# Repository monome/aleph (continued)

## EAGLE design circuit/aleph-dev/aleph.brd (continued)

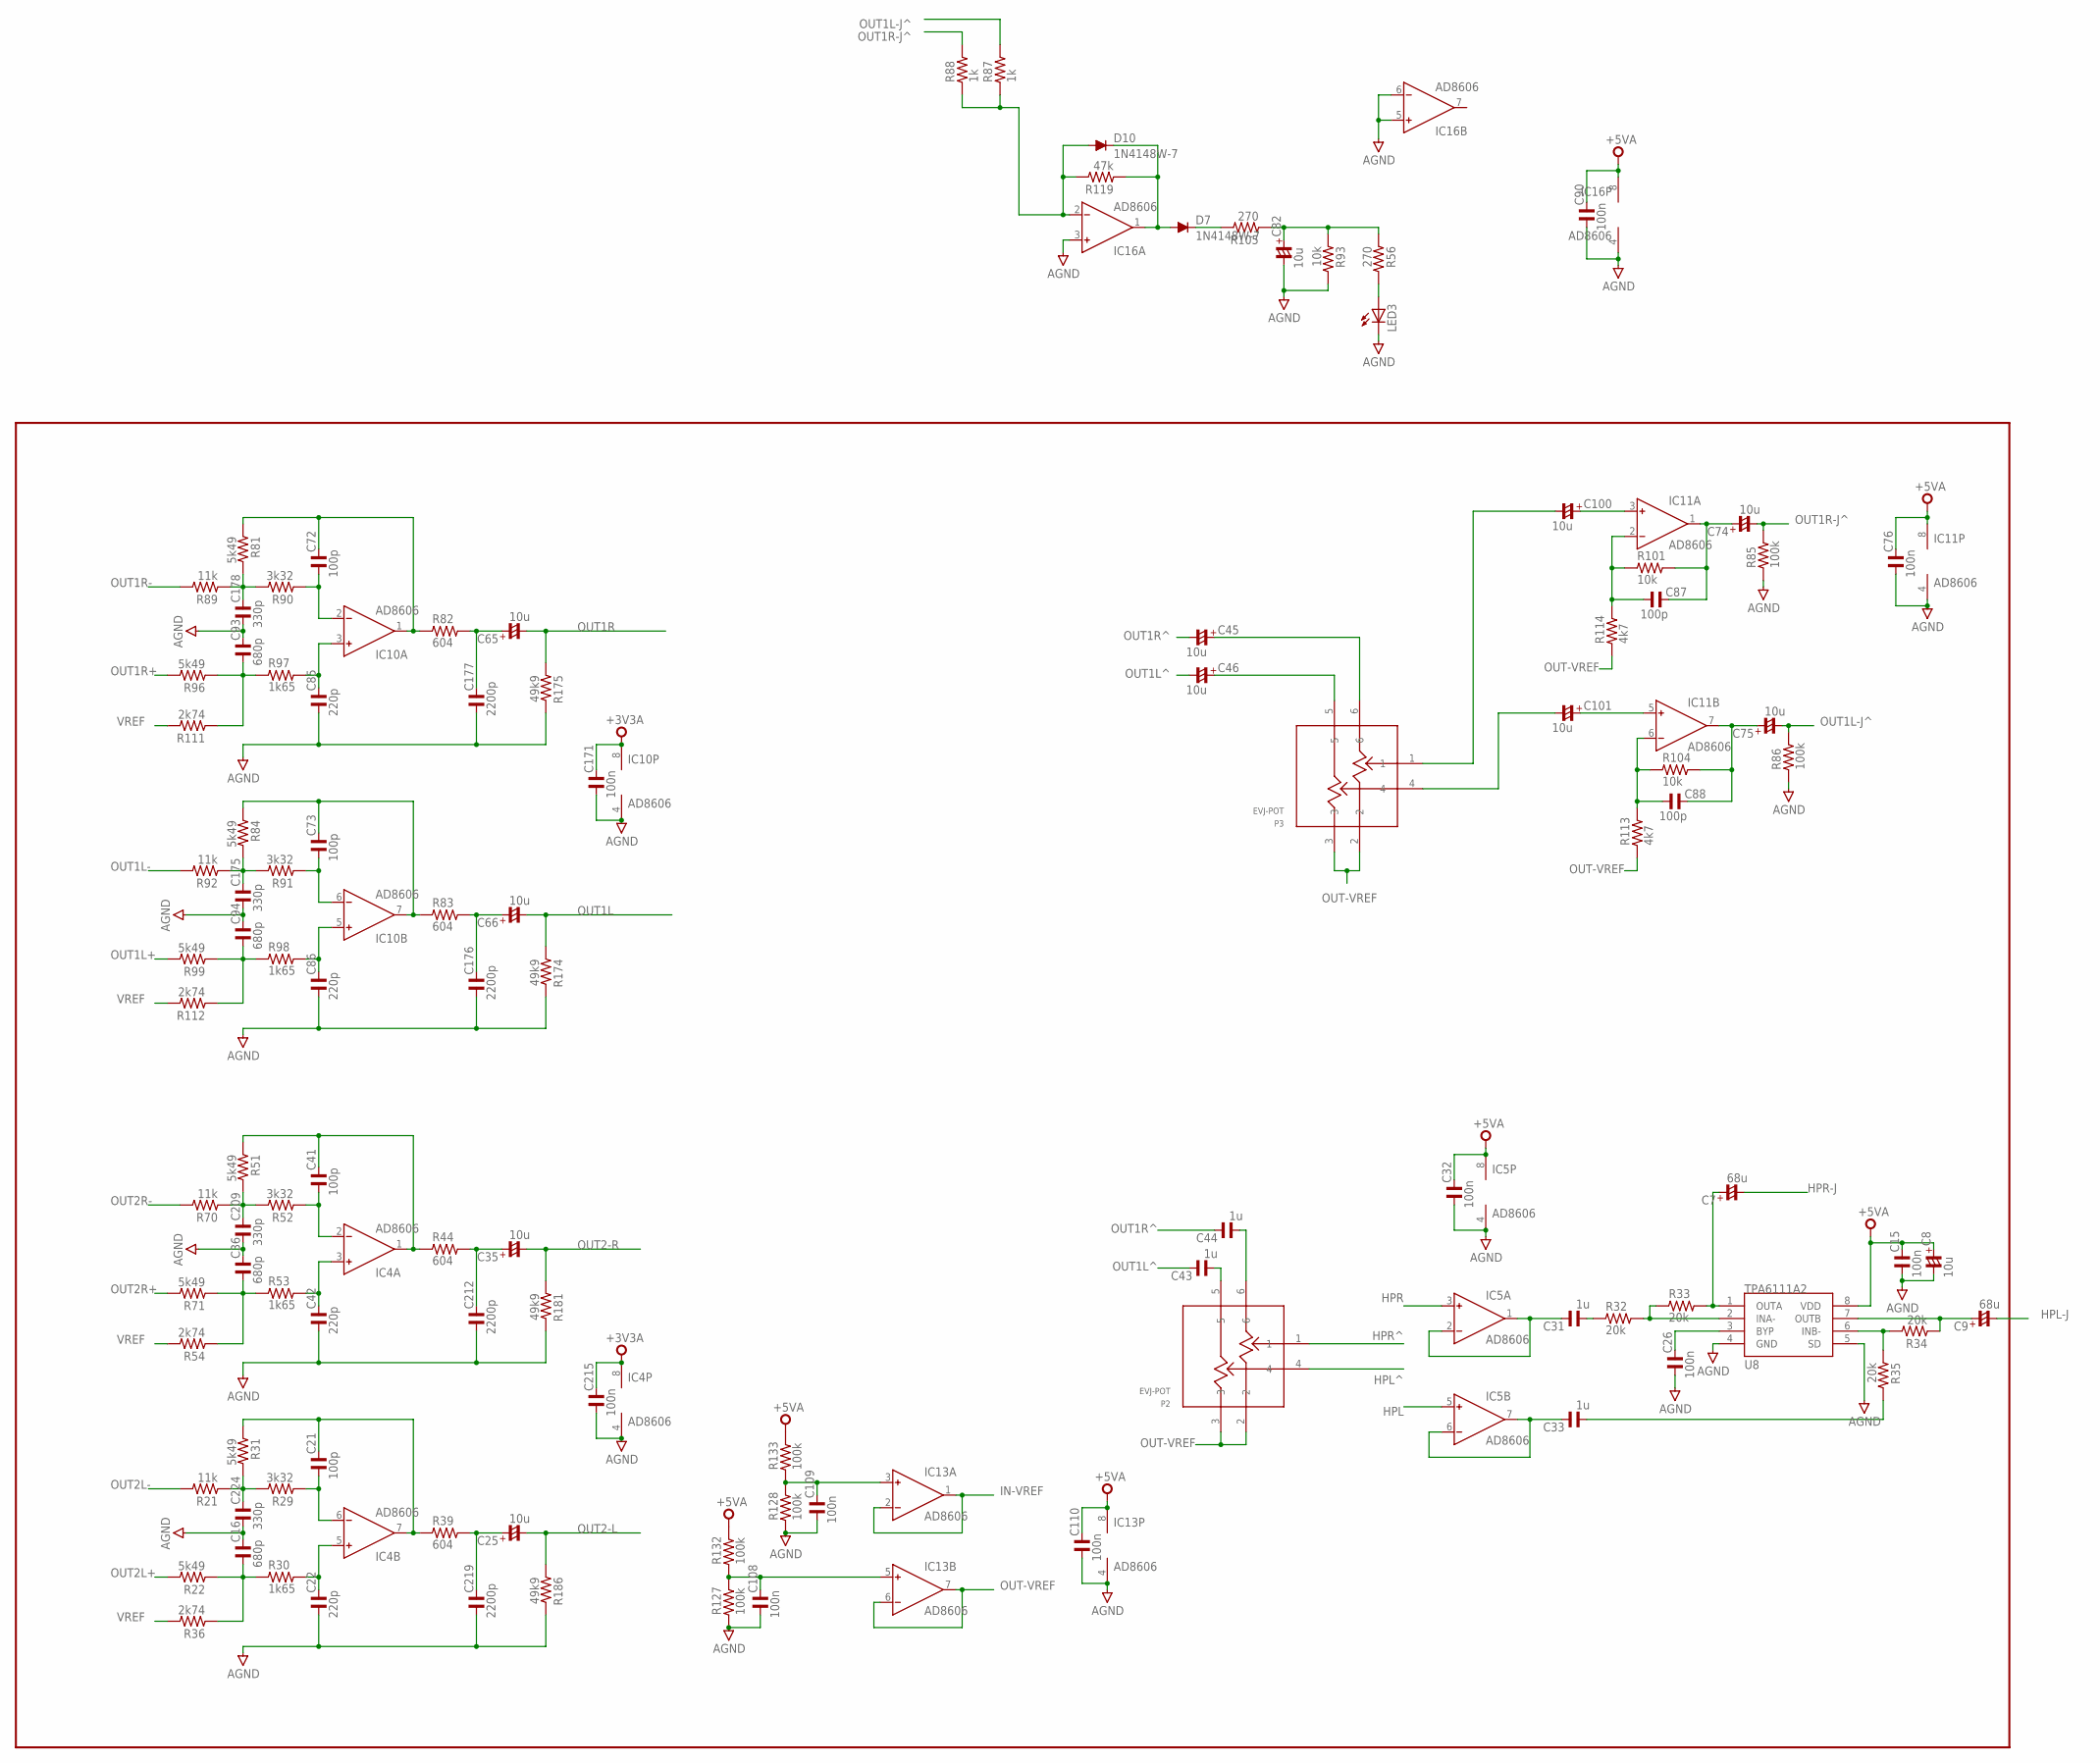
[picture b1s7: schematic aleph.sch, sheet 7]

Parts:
C7, C9: 68u; C1206/T
C8, C25, C35, C45, C46, C65, C66, C74, C75, C82, C100, C101: 10u; C1206/T
C15, C26, C32, C76, C90, C108, C109, C110, C171, C215: 100n; C0603
C16, C36, C93, C94: 680p; C0603
C21, C41, C72, C73, C87, C88: 100p; C0603
C22, C42, C85, C86: 220p; C0603
C31, C33, C43, C44: 1u; C0603
C175, C178, C209, C224: 330p; C0603
C176, C177, C212, C219: 2200p; C0603
D7, D10: 1N4148W-7; SOD123
IC4, IC5, IC10, IC11, IC13, IC16: AD8606; SO8
LED3: LEDCHIPLED_0805; CHIPLED_0805
P2, P3: EVJ-POT
R21, R70, R89, R92: 11k; R0603
R22, R31, R51, R71, R81, R84, R96, R99: 5k49; R0603
R29, R52, R90, R91: 3k32; R0603
R30, R53, R97, R98: 1k65; R0603
R32, R33, R34, R35: 20k; R0603
R36, R54, R111, R112: 2k74; R0603
R39, R44, R82, R83: 604; R0603
R56, R105: 270; R0603
R85, R86, R127, R128, R132, R133: 100k; R0603
R87, R88: 1k; R0603
R93, R101, R104: 10k; R0603
R113, R114: 4k7; R0603
R119: 47k; R0603
R174, R175, R181, R186: 49k9; R0603
U8: TPA6111A2; SO08

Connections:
+3V3A: C171.2, C215.2, IC4.8 (V+), IC10.8 (V+); also elsewhere on the board
+5VA: C8.+, C15.2, C32.2, C76.2, C90.2, C110.2, IC5.8 (V+), IC11.8 (V+), IC13.8 (V+), IC16.8 (V+), R132.2, R133.2, U8.8 (VDD); also elsewhere on the board
AGND: C8.-, C15.1, C16.2, C22.1, C26.1, C32.1, C36.2, C42.1, C76.1, C82.-, C85.1, C86.1, C90.1, C93.2, C94.2, C108.1, C109.1, C110.1, C171.1, C175.1, C176.1, C177.1, C178.1, C209.1, C212.1, C215.1, C219.1, C224.1, IC4.4 (V-), IC5.4 (V-), IC10.4 (V-), IC11.4 (V-), IC13.4 (V-), IC16.3 (IN+), IC16.4 (V-), IC16.5 (IN+), IC16.6 (IN-), LED3.C, R85.1, R86.1, R93.2, R127.1, R128.1, R174.2, R175.2, R181.2, R186.2, U8.4 (GND), U8.5 (SD); also elsewhere on the board
HPL: IC5.5 (IN+); also elsewhere on the board
HPL-J: C9.-; also elsewhere on the board
HPL^: P2.4; also elsewhere on the board
HPR: IC5.3 (IN+); also elsewhere on the board
HPR-J: C7.-; also elsewhere on the board
HPR^: P2.1; also elsewhere on the board
IN-VREF: IC13.1 (OUT), IC13.2 (IN-); also elsewhere on the board
unnamed: C45.+, P3.6
unnamed: C46.+, P3.5
unnamed: C100.-, P3.1
unnamed: C101.+, IC11.5 (IN+)
unnamed: C178.2, R81.2, R89.1, R90.2
unnamed: C93.1, R96.1, R97.1, R111.1
unnamed: C85.2, IC10.3 (IN+), R97.2
unnamed: C72.2, IC10.1 (OUT), R81.1, R82.1
unnamed: C65.+, C177.2, R82.2
unnamed: C175.2, R84.2, R91.2, R92.1
unnamed: C72.1, IC10.2 (IN-), R90.1
unnamed: C94.1, R98.1, R99.1, R112.1
unnamed: C86.2, IC10.5 (IN+), R98.2
unnamed: C73.2, IC10.7 (OUT), R83.1, R84.1
unnamed: C66.+, C176.2, R83.2
unnamed: C73.1, IC10.6 (IN-), R91.1
unnamed: C209.2, R51.2, R52.2, R70.1
unnamed: C36.1, R53.1, R54.1, R71.1
unnamed: C42.2, IC4.3 (IN+), R53.2
unnamed: C41.2, IC4.1 (OUT), R44.1, R51.1
unnamed: C35.+, C212.2, R44.2
unnamed: C41.1, IC4.2 (IN-), R52.1
unnamed: C224.2, R21.1, R29.2, R31.2
unnamed: C16.1, R22.1, R30.1, R36.1
unnamed: C22.2, IC4.5 (IN+), R30.2
unnamed: C75.+, C88.2, IC11.7 (OUT), R104.2
unnamed: C88.1, IC11.6 (IN-), R104.1, R113.2
unnamed: C101.-, P3.4
unnamed: C21.2, IC4.7 (OUT), R31.1, R39.1
unnamed: C100.+, IC11.3 (IN+)
unnamed: C25.+, C219.2, R39.2
unnamed: C21.1, IC4.6 (IN-), R29.1
unnamed: C74.+, C87.2, IC11.1 (OUT), R101.2
unnamed: C87.1, IC11.2 (IN-), R101.1, R114.2
unnamed: C26.2, U8.3 (BYP)
unnamed: C31.2, IC5.1 (OUT), IC5.2 (IN-)
unnamed: C33.2, IC5.6 (IN-), IC5.7 (OUT)
unnamed: C33.1, R35.2
unnamed: C31.1, R32.1
unnamed: R32.2, R33.1, U8.2 (INA-)
unnamed: C7.+, R33.2, U8.1 (OUTA)
unnamed: C43.1, P2.5
unnamed: R34.2, R35.1, U8.6 (INB-)
unnamed: C44.1, P2.6
unnamed: C109.2, IC13.3 (IN+), R128.2, R133.1
unnamed: C9.+, R34.1, U8.7 (OUTB)
unnamed: C108.2, IC13.5 (IN+), R127.2, R132.1
unnamed: D10.A, IC16.2 (IN-), R87.1, R88.1, R119.2
unnamed: D7.A, D10.C, IC16.1 (OUT), R119.1
unnamed: D7.C, R105.2
unnamed: C82.+, R56.1, R93.1, R105.1
unnamed: LED3.A, R56.2
OUT1L: C66.-, R174.1; also elsewhere on the board
OUT1L+: R99.2; also elsewhere on the board
OUT1L-: R92.2; also elsewhere on the board
OUT1L-J^: C75.-, R86.2, R87.2; also elsewhere on the board
OUT1L^: C43.2, C46.-; also elsewhere on the board
OUT1R: C65.-, R175.1; also elsewhere on the board
OUT1R+: R96.2; also elsewhere on the board
OUT1R-: R89.2; also elsewhere on the board
OUT1R-J^: C74.-, R85.2, R88.2; also elsewhere on the board
OUT1R^: C44.2, C45.-; also elsewhere on the board
OUT2-L: C25.-, R186.1; also elsewhere on the board
OUT2-R: C35.-, R181.1; also elsewhere on the board
OUT2L+: R22.2; also elsewhere on the board
OUT2L-: R21.2; also elsewhere on the board
OUT2R+: R71.2; also elsewhere on the board
OUT2R-: R70.2; also elsewhere on the board
OUT-VREF: IC13.6 (IN-), IC13.7 (OUT), P2.2, P2.3, P3.2, P3.3, R113.1, R114.1
VREF: R36.2, R54.2, R111.2, R112.2; also elsewhere on the board

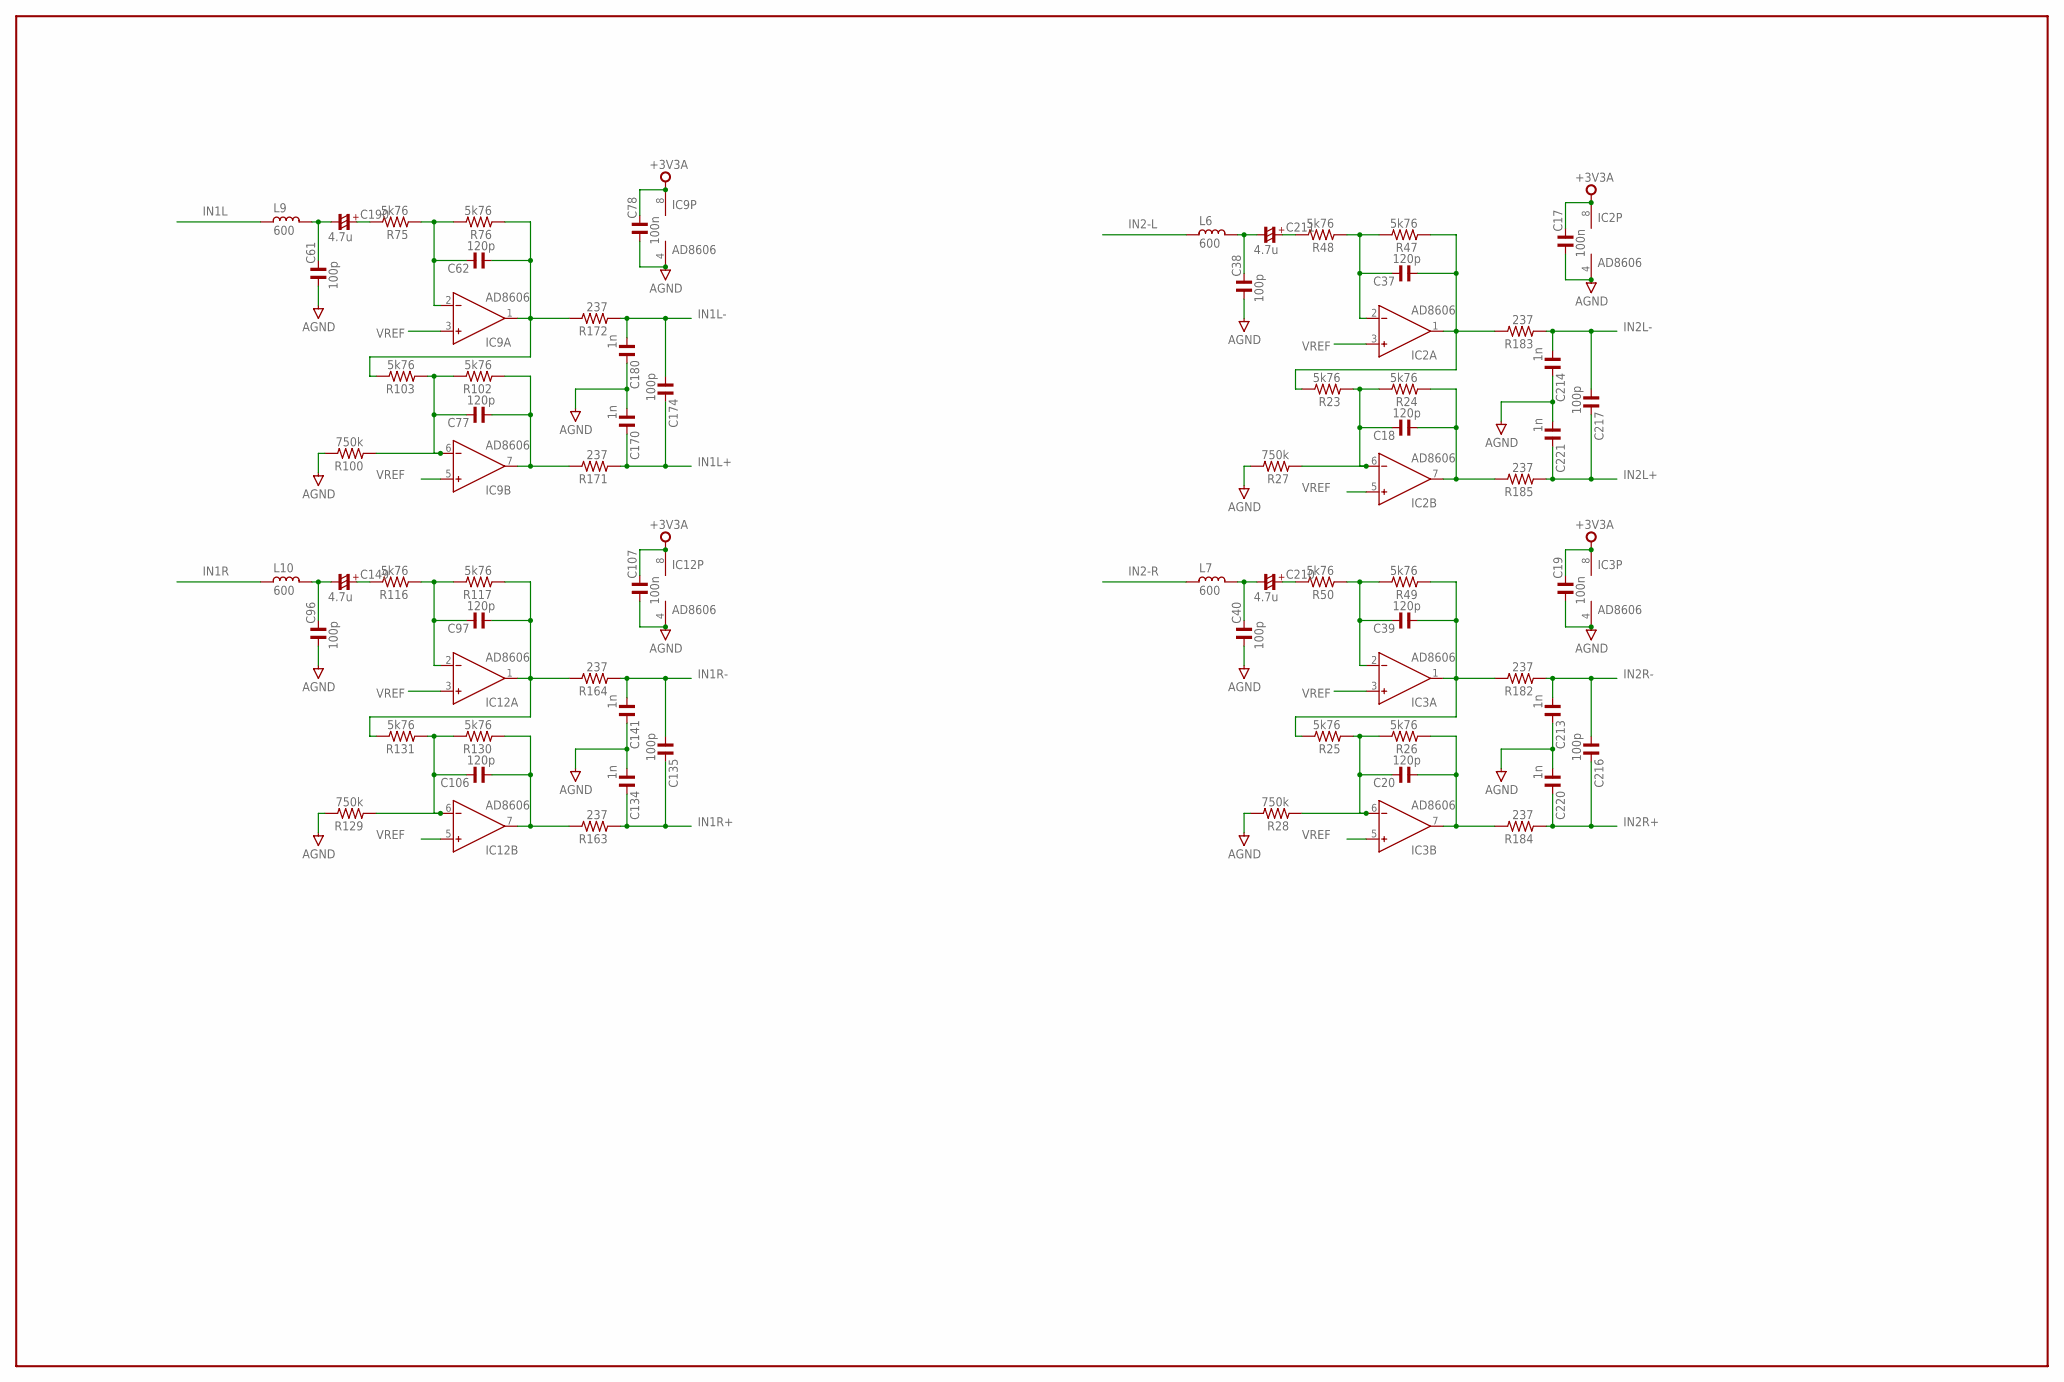
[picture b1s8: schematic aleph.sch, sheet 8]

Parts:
C17, C19, C78, C107: 100n; C0603
C18, C20, C37, C39, C62, C77, C97, C106: 120p; C0603
C38, C40, C61, C96, C135, C174, C216, C217: 100p; C0603
C134, C141, C170, C180, C213, C214, C220, C221: 1n; C0603
C149, C190, C210, C211: 4.7u; C1206/T
IC2, IC3, IC9, IC12: AD8606; SO8
L6, L7, L9, L10: 600; L0603
R23, R24, R25, R26, R47, R48, R49, R50, R75, R76, R102, R103, R116, R117, R130, R131: 5k76; R0603
R27, R28, R100, R129: 750k; R0603
R163, R164, R171, R172, R182, R183, R184, R185: 237; R0603

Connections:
+3V3A: C17.2, C19.2, C78.2, C107.2, IC2.8 (V+), IC3.8 (V+), IC9.8 (V+), IC12.8 (V+); also elsewhere on the board
AGND: C17.1, C19.1, C38.1, C40.1, C61.1, C78.1, C96.1, C107.1, C134.1, C141.2, C170.1, C180.2, C213.2, C214.2, C220.1, C221.1, IC2.4 (V-), IC3.4 (V-), IC9.4 (V-), IC12.4 (V-), R27.2, R28.2, R100.2, R129.2; also elsewhere on the board
IN1L: L9.2; also elsewhere on the board
IN1L+: C170.2, C174.2, R171.1; also elsewhere on the board
IN1L-: C174.1, C180.1, R172.1; also elsewhere on the board
IN1R: L10.2; also elsewhere on the board
IN1R+: C134.2, C135.2, R163.1; also elsewhere on the board
IN1R-: C135.1, C141.1, R164.1; also elsewhere on the board
IN2-L: L6.2; also elsewhere on the board
IN2-R: L7.2; also elsewhere on the board
IN2L+: C217.2, C221.2, R185.1; also elsewhere on the board
IN2L-: C214.1, C217.1, R183.1; also elsewhere on the board
IN2R+: C216.2, C220.2, R184.1; also elsewhere on the board
IN2R-: C213.1, C216.1, R182.1; also elsewhere on the board
unnamed: C190.+, R75.2
unnamed: C97.1, IC12.1 (OUT), R117.1, R131.2, R164.2
unnamed: C106.1, IC12.7 (OUT), R130.1, R163.2
unnamed: C96.2, C149.-, L10.1
unnamed: C97.2, IC12.2 (IN-), R116.1, R117.2
unnamed: C106.2, IC12.6 (IN-), R129.1, R130.2, R131.1
unnamed: C149.+, R116.2
unnamed: C62.1, IC9.1 (OUT), R76.1, R103.2, R172.2
unnamed: C77.1, IC9.7 (OUT), R102.1, R171.2
unnamed: C61.2, C190.-, L9.1
unnamed: C62.2, IC9.2 (IN-), R75.1, R76.2
unnamed: C77.2, IC9.6 (IN-), R100.1, R102.2, R103.1
unnamed: C37.1, IC2.1 (OUT), R23.2, R47.1, R183.2
unnamed: C18.1, IC2.7 (OUT), R24.1, R185.2
unnamed: C38.2, C211.-, L6.1
unnamed: C37.2, IC2.2 (IN-), R47.2, R48.1
unnamed: C18.2, IC2.6 (IN-), R23.1, R24.2, R27.1
unnamed: C211.+, R48.2
unnamed: C39.1, IC3.1 (OUT), R25.2, R49.1, R182.2
unnamed: C20.1, IC3.7 (OUT), R26.1, R184.2
unnamed: C40.2, C210.-, L7.1
unnamed: C39.2, IC3.2 (IN-), R49.2, R50.1
unnamed: C20.2, IC3.6 (IN-), R25.1, R26.2, R28.1
unnamed: C210.+, R50.2
VREF: IC2.3 (IN+), IC2.5 (IN+), IC3.3 (IN+), IC3.5 (IN+), IC9.3 (IN+), IC9.5 (IN+), IC12.3 (IN+), IC12.5 (IN+); also elsewhere on the board

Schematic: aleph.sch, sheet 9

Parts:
C53, C55, C91, C92: 100n; C0603
C54, C56, C57, C58, C63, C64, C83, C84: 10u; C1206/T
C59, C60: 100p; C0603
D8, D9, D11, D12: 1N4148W-7; SOD123
IC6, IC7, IC14, IC15: AD8606; SO8
J10: PHA2U
LED4, LED5, LED6, LED7: LEDCHIPLED_0805; CHIPLED_0805
P4, P5: EVJ-POT
R5, R14, R94, R95: 10k; R0603
R9, R12, R120, R121: 47k; R0603
R57, R58, R59, R60, R106, R107: 270; R0603
R73, R74, R123, R125: 100k; R0603
R77, R78: 470k; R0603
R79, R80: 4k7; R0603
R122, R124: 56k; R0603

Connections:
+5VA: C53.2, C55.2, C91.2, C92.2, IC6.8 (V+), IC7.8 (V+), IC14.8 (V+), IC15.8 (V+), LED5.A, LED7.A, R122.1, R124.1; also elsewhere on the board
AGND: C53.1, C55.1, C83.-, C84.-, C91.1, C92.1, IC6.4 (V-), IC7.4 (V-), IC14.3 (IN+), IC14.4 (V-), IC15.3 (IN+), IC15.4 (V-), LED4.C, LED6.C, R73.1, R74.1, R94.2, R95.2, R123.2, R125.2; also elsewhere on the board
GAINL-1: C54.+, C59.1, IC6.7 (OUT), J10._0
GAINL-2: C59.2, IC6.6 (IN-), R12.1, R14.1, R79.2
GAINR-1: C56.+, C60.1, IC7.7 (OUT), J10.0
GAINR-2: C60.2, IC7.6 (IN-), R5.1, R9.1, R80.2
IN1L-J^: C57.-; also elsewhere on the board
IN1L^: C54.-, D11.A, IC15.2 (IN-), R73.2, R120.2; also elsewhere on the board
IN1R-J^: C58.-; also elsewhere on the board
IN1R^: C56.-, D12.A, IC14.2 (IN-), R74.2, R121.2; also elsewhere on the board
IN-VREF: P4.2, P4.3, P5.2, P5.3, R77.1, R78.1, R79.1, R80.1; also elsewhere on the board
unnamed: C57.+, IC6.3 (IN+), R77.2
unnamed: IC6.1 (OUT), IC6.2 (IN-), P4.6
unnamed: C63.-, IC6.5 (IN+)
unnamed: D8.A, D11.C, IC15.1 (OUT), R120.1
unnamed: LED7.C, R60.2
unnamed: C63.+, P4.1
unnamed: D8.C, R106.2
unnamed: C83.+, IC15.6 (IN-), R57.1, R94.1, R106.1
unnamed: LED5.C, R58.2
unnamed: C58.+, IC7.3 (IN+), R78.2
unnamed: J10._2, R12.2
unnamed: IC7.1 (OUT), IC7.2 (IN-), P5.6
unnamed: LED4.A, R57.2
unnamed: J10._1, R14.2
unnamed: J10.2, R9.2
unnamed: J10.1, R5.2
unnamed: IC15.7 (OUT), R58.1
unnamed: IC15.5 (IN+), R122.2, R123.1
unnamed: C64.-, IC7.5 (IN+)
unnamed: C64.+, P5.1
unnamed: D9.A, D12.C, IC14.1 (OUT), R121.1
unnamed: D9.C, R107.2
unnamed: C84.+, IC14.6 (IN-), R59.1, R95.1, R107.1
unnamed: LED6.A, R59.2
unnamed: IC14.7 (OUT), R60.1
unnamed: IC14.5 (IN+), R124.2, R125.1

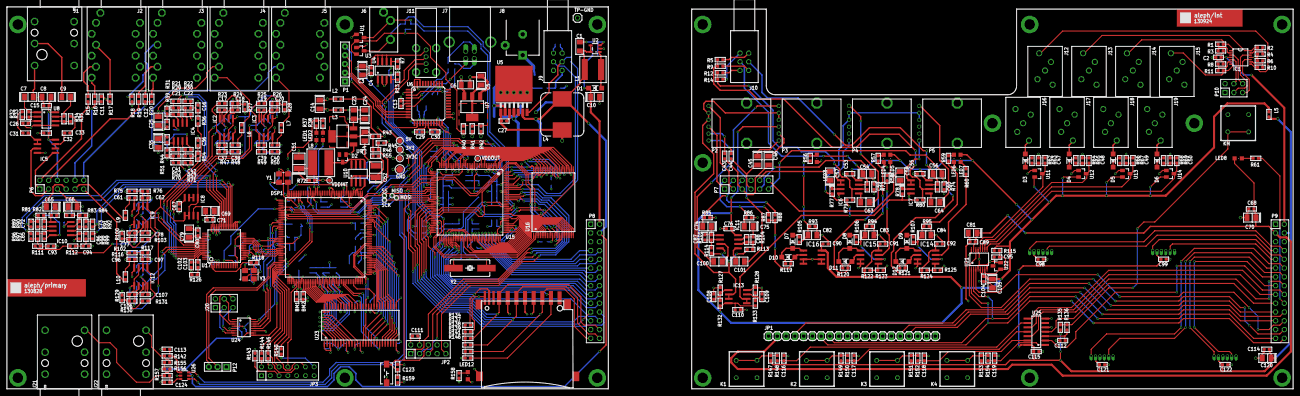
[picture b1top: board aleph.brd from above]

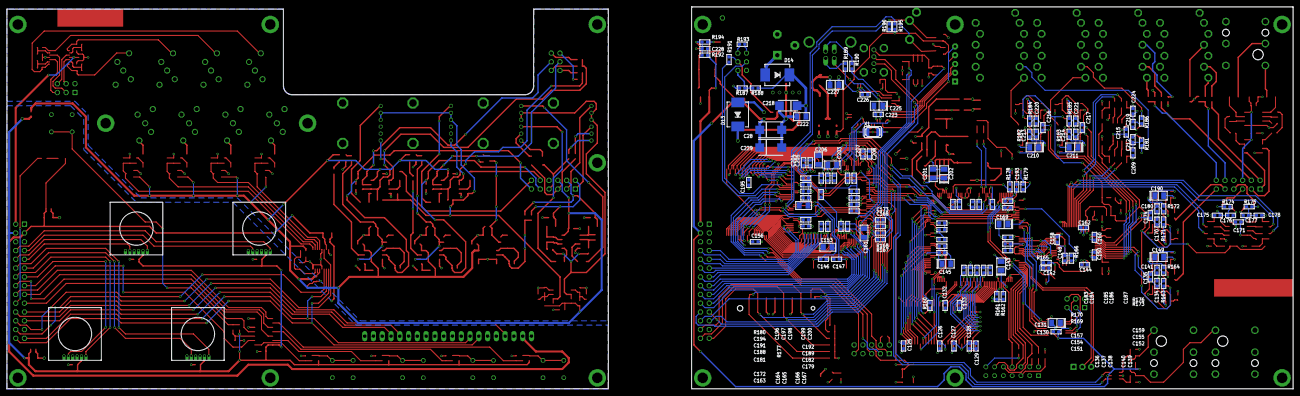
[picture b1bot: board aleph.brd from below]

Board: 4 copper layers, 372.1 x 110.5 mm, 571 parts (150 on the bottom side), 443 nets.

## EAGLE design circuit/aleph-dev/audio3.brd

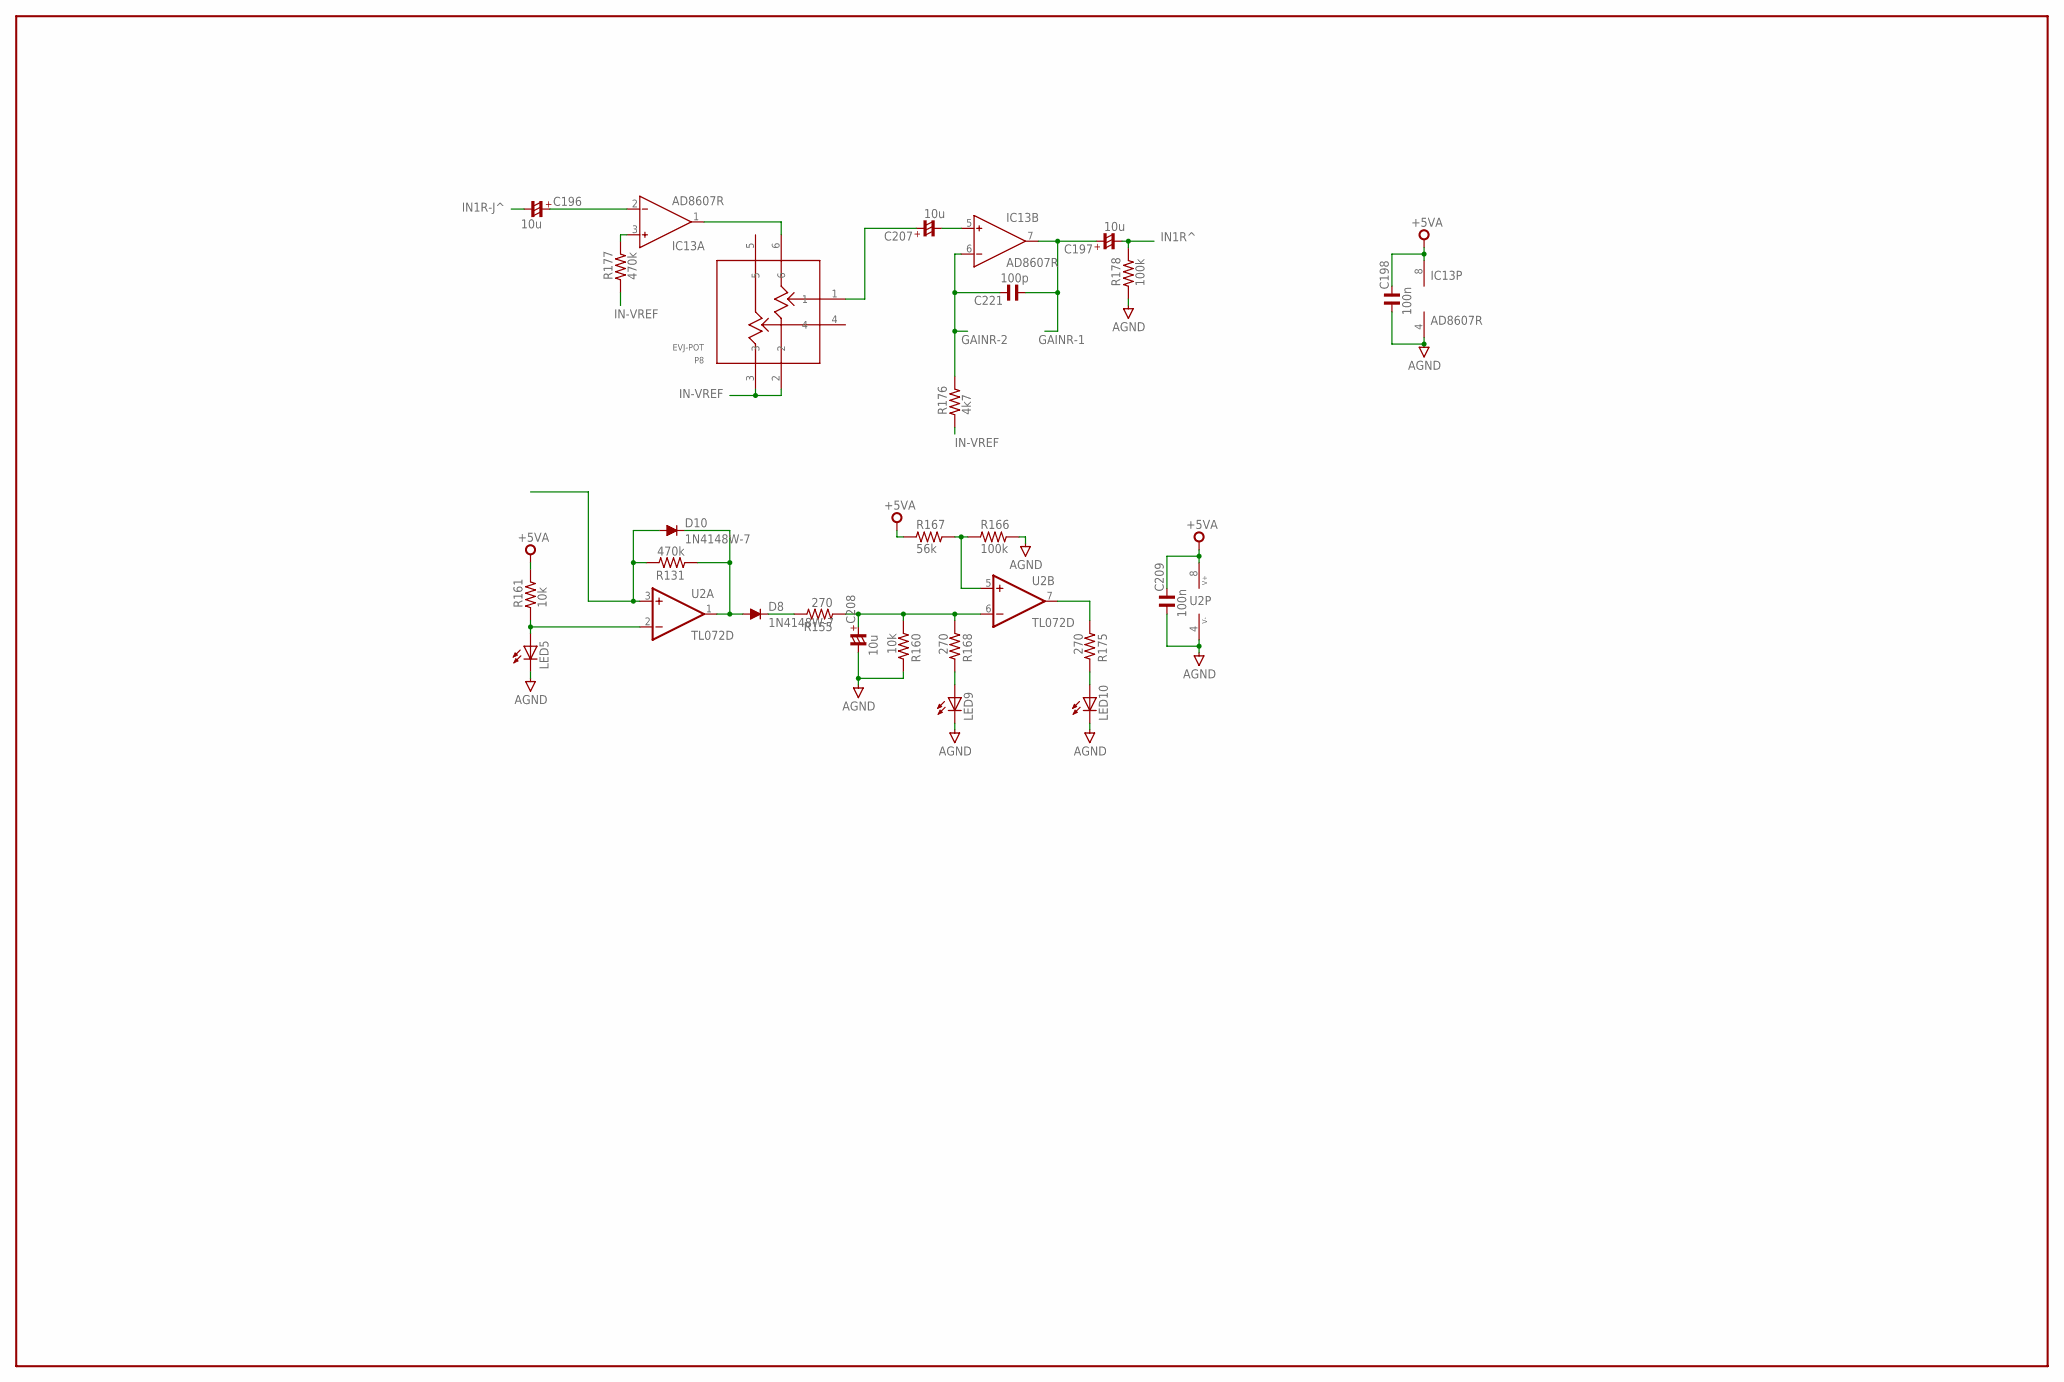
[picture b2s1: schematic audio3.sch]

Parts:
C196, C197, C207, C208: 10u; C1206/T
C198, C209: 100n; C0603
C221: 100p; C0603
D8, D10: 1N4148W-7; SOD123
IC13: AD8607R; SO8
LED5, LED9, LED10: LEDCHIPLED_0805; CHIPLED_0805
P8: EVJ-POT
R131, R177: 470k; R0603
R155, R168, R175: 270; R0603
R160, R161: 10k; R0603
R166, R178: 100k; R0603
R167: 56k; R0603
R176: 4k7; R0603
U2: TL072D; SO08

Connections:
+5VA: C198.2, C209.2, IC13.8 (V+), R161.2, R167.1, U2.8 (V+)
AGND: C198.1, C208.-, C209.1, IC13.4 (V-), LED5.C, LED9.C, LED10.C, R160.2, R166.2, R178.1, U2.4 (V-)
GAINR-1: C197.+, C221.1, IC13.7 (OUT)
GAINR-2: C221.2, IC13.6 (IN-), R176.2
IN1R-J^: C196.-
IN1R^: C197.-, R178.2
IN-VREF: P8.2, P8.3, R176.1, R177.1
unnamed: IC13.3 (IN+), R177.2
unnamed: D10.A, R131.2, U2.3 (+IN)
unnamed: IC13.1 (OUT), P8.6
unnamed: C207.-, IC13.5 (IN+)
unnamed: D8.A, D10.C, R131.1, U2.1 (OUT)
unnamed: C196.+, IC13.2 (IN-)
unnamed: C207.+, P8.1
unnamed: D8.C, R155.2
unnamed: C208.+, R155.1, R160.1, R168.1, U2.6 (-IN)
unnamed: LED5.A, R161.1, U2.2 (-IN)
unnamed: LED9.A, R168.2
unnamed: LED10.A, R175.2
unnamed: R175.1, U2.7 (OUT)
unnamed: R166.1, R167.2, U2.5 (+IN)

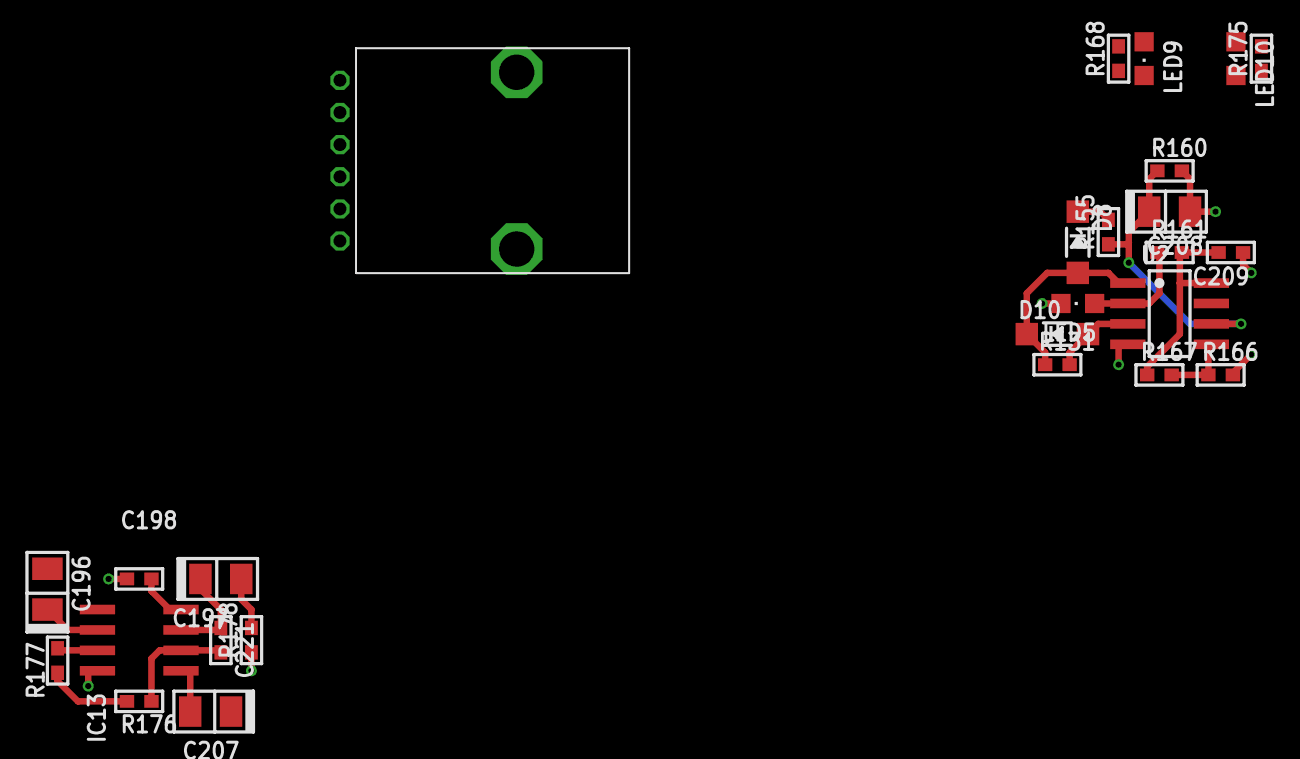
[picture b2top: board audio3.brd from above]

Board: 4 copper layers, 26 parts (0 on the bottom side), 20 nets.

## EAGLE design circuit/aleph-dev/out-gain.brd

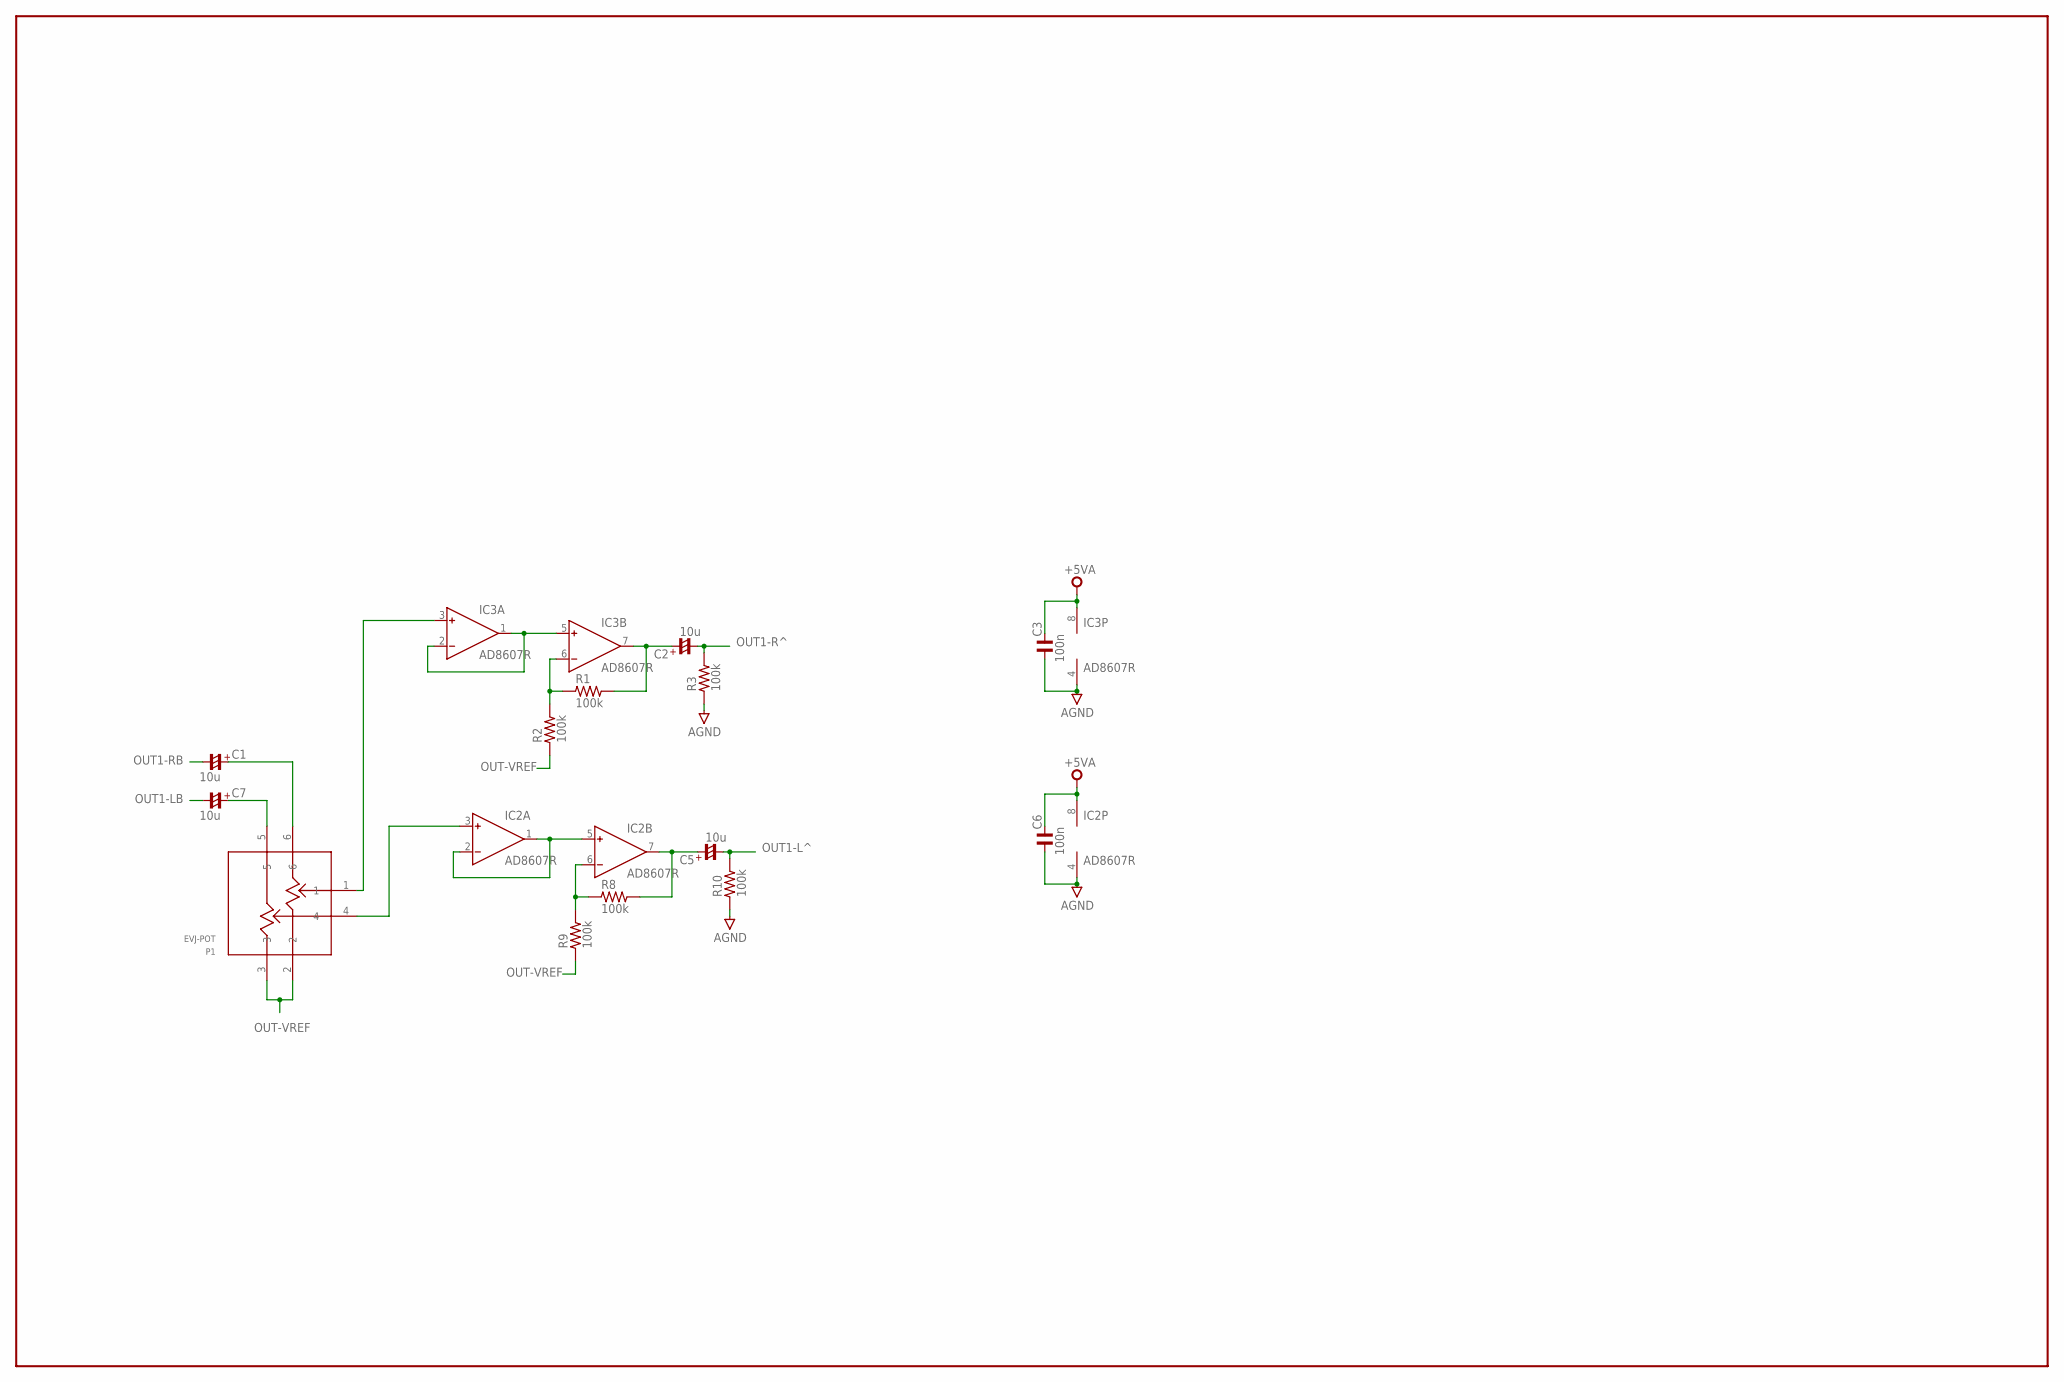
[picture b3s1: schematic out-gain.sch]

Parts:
C1, C2, C5, C7: 10u; C1206/T
C3, C6: 100n; C0603
IC2, IC3: AD8607R; SO8
P1: EVJ-POT
R1, R2, R3, R8, R9, R10: 100k; R0603

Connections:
+5VA: C3.2, C6.2, IC2.8 (V+), IC3.8 (V+)
AGND: C3.1, C6.1, IC2.4 (V-), IC3.4 (V-), R3.1, R10.1
unnamed: IC3.3 (IN+), P1.1
unnamed: IC3.1 (OUT), IC3.2 (IN-), IC3.5 (IN+)
unnamed: C2.+, IC3.7 (OUT), R1.2
unnamed: IC3.6 (IN-), R1.1, R2.2
unnamed: C1.+, P1.6
unnamed: IC2.3 (IN+), P1.4
unnamed: C7.+, P1.5
unnamed: IC2.1 (OUT), IC2.2 (IN-), IC2.5 (IN+)
unnamed: C5.+, IC2.7 (OUT), R8.2
unnamed: IC2.6 (IN-), R8.1, R9.2
OUT1-LB: C7.-
OUT1-L^: C5.-, R10.2
OUT1-RB: C1.-
OUT1-R^: C2.-, R3.2
OUT-VREF: P1.2, P1.3, R2.1, R9.1

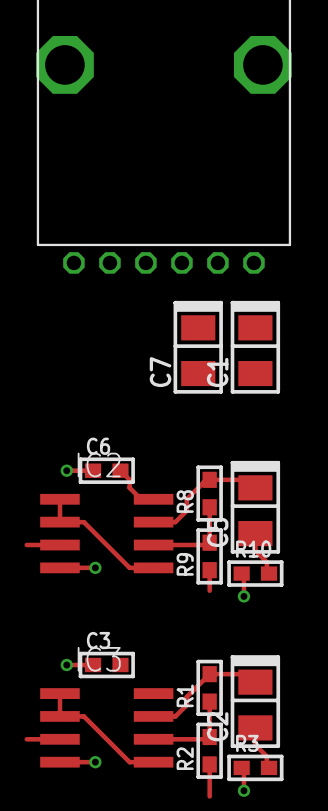
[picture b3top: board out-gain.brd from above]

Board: 4 copper layers, 15 parts (0 on the bottom side), 15 nets.
